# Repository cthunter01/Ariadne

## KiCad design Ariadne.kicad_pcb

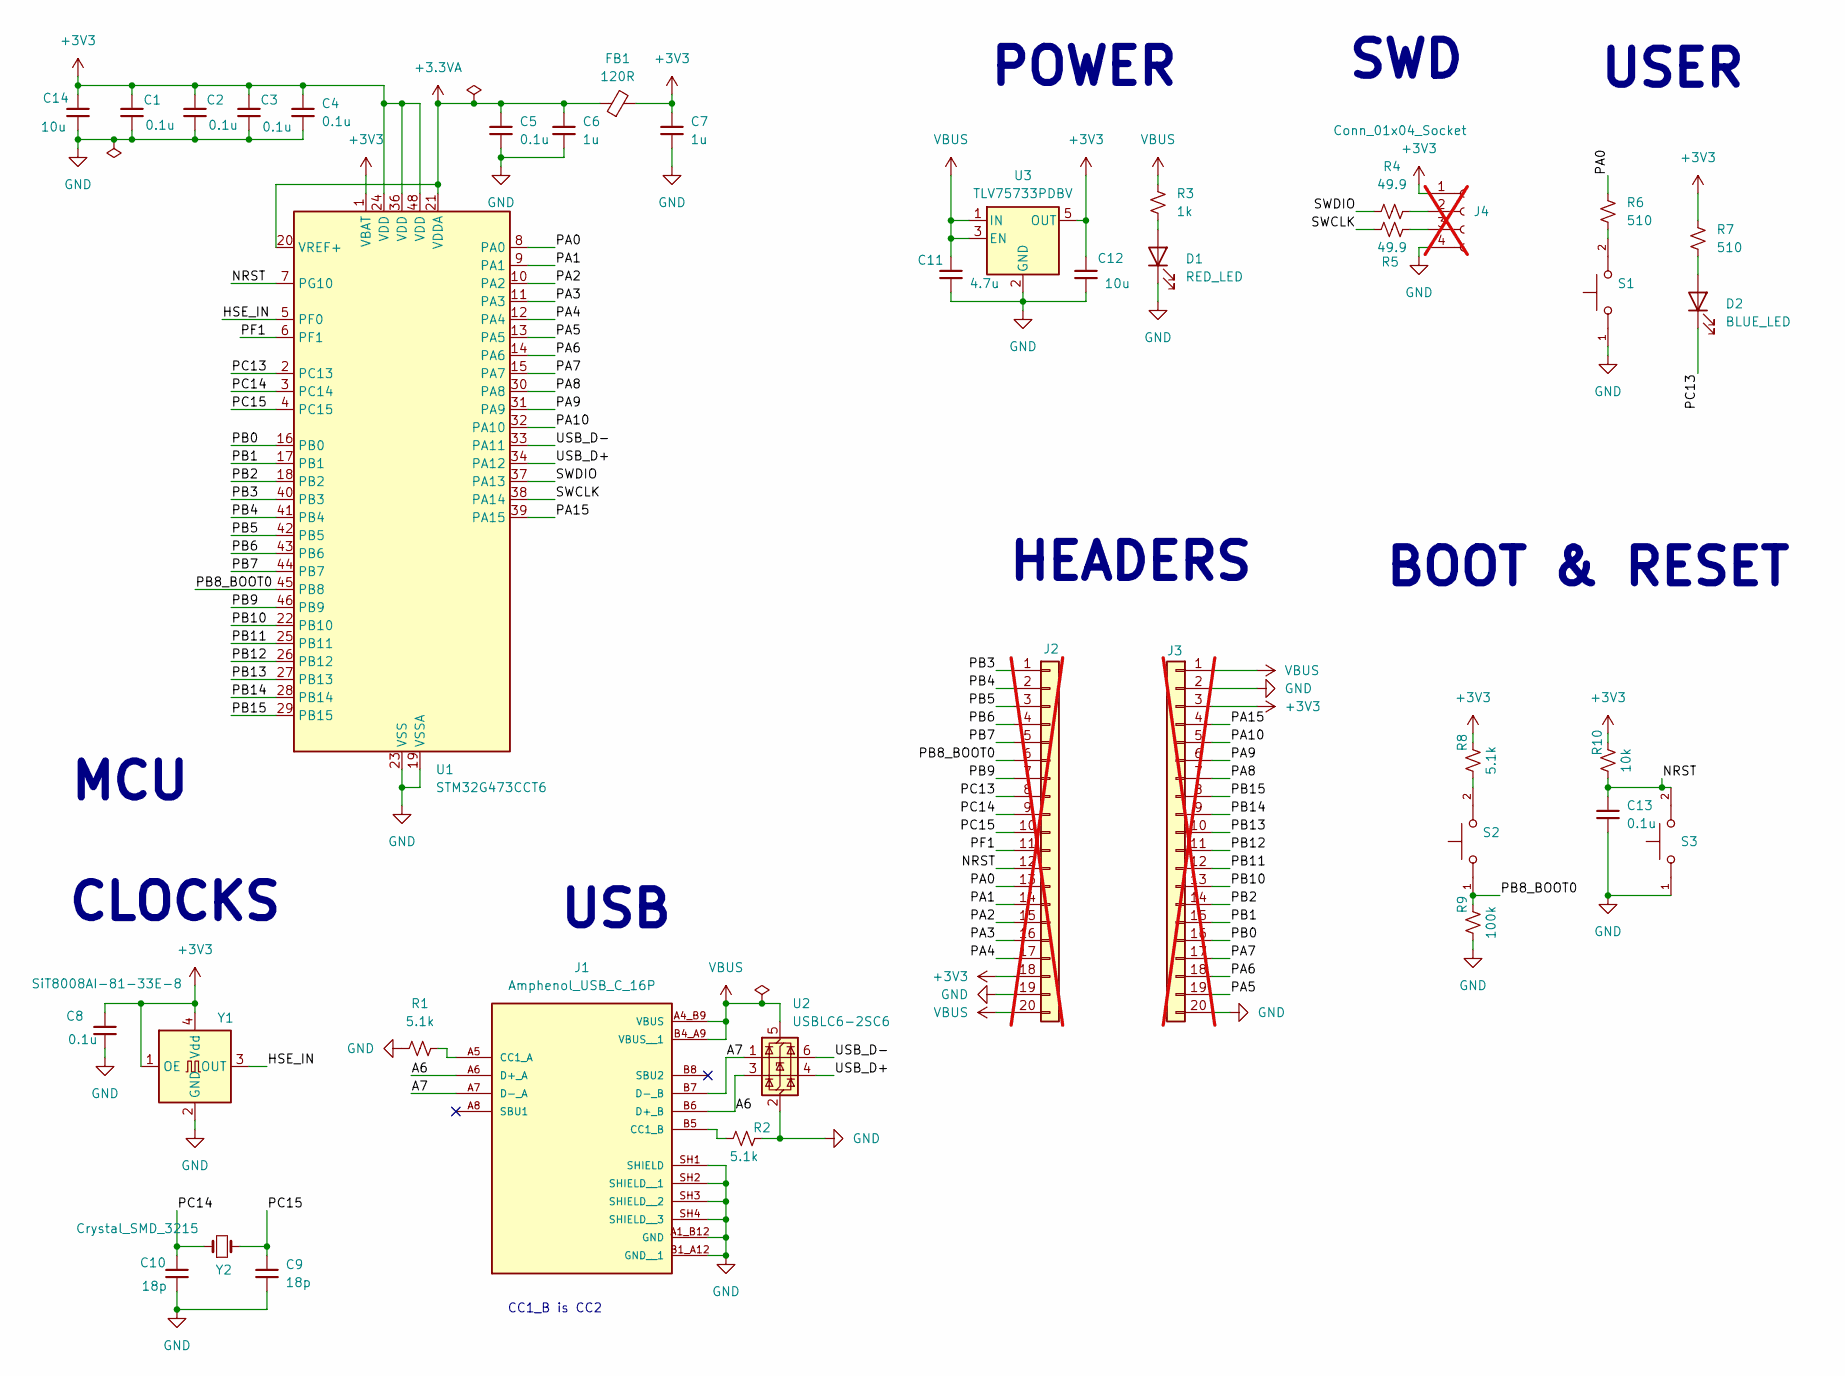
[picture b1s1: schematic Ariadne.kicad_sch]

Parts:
C1, C2, C3, C4, C5, C8, C13: 0.1u; C_0402_1005Metric; MPN CL05B104KO5NNNC; LCSC Part # C1525
C6, C7: 1u; C_0402_1005Metric; MPN CL05A105KA5NQNC; LCSC Part # C52923
C9, C10: 18p; C_0402_1005Metric; MPN 0402CG180J500NT; LCSC Part # C1549
C11: 4.7u; C_0402_1005Metric; MPN CL05A475MO5NUNC; LCSC Part # C318563
C12: 10u; C_0402_1005Metric; MPN CL05A106MP5NUNC; LCSC Part # C315248
C14: 10u; C_0603_1608Metric; MPN CL10A106KP8NNNC; LCSC Part # C19702
D1: RED_LED; LED_0402_1005Metric; MPN MHT136CRCT; LCSC Part # C397045
D2: BLUE_LED; LED_0402_1005Metric; MPN NCD0402B1; LCSC Part # C130724
FB1: 120R; IND_BLM18_0603_MUR; MPN BLM18PG121SN1D; LCSC Part # C14709
J1: Amphenol_USB_C_16P; AMPHENOL_12402012E212A; PARTREV 4; LCSC Part # C5150972
J2, J3: Conn_01x20; PinHeader_1x20_P2.54mm_Vertical; not fitted
J4: Conn_01x04_Socket; PinSocket_1x04_P2.54mm_Horizontal; not fitted
R1, R2, R8: 5.1k; R_0402_1005Metric; MPN 0402WGF5101TCE; LCSC Part # C25905
R3: 1k; R_0402_1005Metric; MPN 0402WGF1001TCE; LCSC Part # C11702
R4, R5: 49.9; R_0402_1005Metric; MPN 0402WGF499JTCE; LCSC Part # C25120
R6, R7: 510; R_0402_1005Metric; MPN 0402WGF5100TCE; LCSC Part # C25123
R9: 100k; R_0402_1005Metric; MPN 0402WGF1003TCE; LCSC Part # C25741
R10: 10k; R_0402_1005Metric; MPN 0402WGF1002TCE; LCSC Part # C25744
S1, S2, S3: TS-1088R-02026; SW_SWT0110-020010SSA_REVA; PARTREV A; LCSC Part # C455280
U1: STM32G473CCT6; STM32G473CCT3; MPN STM32G473CCT6; LCSC Part # C730112
U2: USBLC6-2SC6; SOT-23-6; MPN USBLC6-2SC6; LCSC Part # C7519
U3: TLV75733PDBV; SOT-23-5; MPN TLV75733PDBVR; LCSC Part # C485517
Y1: SiT8008AI-81-33E-8; Oscillator_SMD_SiT_PQFN-4Pin_7.0x5.0mm; MPN SiT8008AI-81-33E-8.000000; LCSC Part # C825363
Y2: Crystal_SMD_3215; Crystal_SMD_3215-2Pin_3.2x1.5mm; MPN Q13FC13500004; LCSC Part # C32346

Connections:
+3.3VA: C5.1, C6.1, FB1.1, U1.20 (VREF+), U1.21 (VDDA)
+3V3: C1.1, C2.1, C3.1, C4.1, C7.1, C8.1, C12.1, C14.1, FB1.2, J2.18, J3.3, J4.1, R7.1, R8.1, R10.1, U1.1 (VBAT), U1.24 (VDD), U1.36 (VDD), U1.48 (VDD), U3.5 (OUT), Y1.1 (OE), Y1.4 (Vdd)
/A6: J1.A6 (D+_A), J1.B6 (D+_B), U2.3 (I/O2)
/A7: J1.A7 (D-_A), J1.B7 (D-_B), U2.1 (I/O1)
/HSE_IN: U1.5 (PF0), Y1.3 (OUT)
/NRST: C13.1, J2.12, R10.2, S3.2, U1.7 (PG10)
/PA0: J2.13, R6.1, U1.8 (PA0)
/PA1: J2.14, U1.9 (PA1)
/PA2: J2.15, U1.10 (PA2)
/PA3: J2.16, U1.11 (PA3)
/PA4: J2.17, U1.12 (PA4)
/PA5: J3.19, U1.13 (PA5)
/PA6: J3.18, U1.14 (PA6)
/PA7: J3.17, U1.15 (PA7)
/PA8: J3.7, U1.30 (PA8)
/PA9: J3.6, U1.31 (PA9)
/PA10: J3.5, U1.32 (PA10)
/PA15: J3.4, U1.39 (PA15)
/PB0: J3.16, U1.16 (PB0)
/PB1: J3.15, U1.17 (PB1)
/PB2: J3.14, U1.18 (PB2)
/PB3: J2.1, U1.40 (PB3)
/PB4: J2.2, U1.41 (PB4)
/PB5: J2.3, U1.42 (PB5)
/PB6: J2.4, U1.43 (PB6)
/PB7: J2.5, U1.44 (PB7)
/PB8_BOOT0: J2.6, R9.1, S2.1, U1.45 (PB8)
/PB9: J2.7, U1.46 (PB9)
/PB10: J3.13, U1.22 (PB10)
/PB11: J3.12, U1.25 (PB11)
/PB12: J3.11, U1.26 (PB12)
/PB13: J3.10, U1.27 (PB13)
/PB14: J3.9, U1.28 (PB14)
/PB15: J3.8, U1.29 (PB15)
/PC13: D2.1 (K), J2.8, U1.2 (PC13)
/PC14: C10.1, J2.9, U1.3 (PC14), Y2.1
/PC15: C9.1, J2.10, U1.4 (PC15), Y2.2
/PF1: J2.11, U1.6 (PF1)
/SWCLK: R5.2, U1.38 (PA14)
/SWDIO: R4.1, U1.37 (PA13)
/USB_D+: U1.34 (PA12), U2.4 (I/O2)
/USB_D-: U1.33 (PA11), U2.6 (I/O1)
GND: C1.2, C2.2, C3.2, C4.2, C5.2, C6.2, C7.2, C8.2, C9.2, C10.2, C11.2, C12.2, C13.2, C14.2, D1.1 (K), J1.A1_B12 (GND), J1.B1_A12 (GND__1), J1.SH1 (SHIELD), J1.SH2 (SHIELD__1), J1.SH3 (SHIELD__2), J1.SH4 (SHIELD__3), J2.19, J3.2, J3.20, J4.4, R1.1, R2.1, R9.2, S1.1, S3.1, U1.19 (VSSA), U1.23 (VSS), U1.35 (VSS), U1.47 (VSS), U2.2 (GND), U3.2 (GND), Y1.2 (GND)
unnamed: D1.2 (A), R3.2
unnamed: D2.2 (A), R7.2
unnamed: J1.A5 (CC1_A), R1.2
unnamed: J1.B5 (CC1_B), R2.2
unnamed: J4.2, R4.2
unnamed: J4.3, R5.1
unnamed: R6.2, S1.2
unnamed: R8.2, S2.2
VBUS: C11.1, J1.A4_B9 (VBUS), J1.B4_A9 (VBUS__1), J2.20, J3.1, R3.1, U2.5 (VBUS), U3.1 (IN), U3.3 (EN)

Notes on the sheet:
POWER
CLOCKS
BOOT & RESET
HEADERS
USER
CC1_B is CC2
SWD
MCU
USB

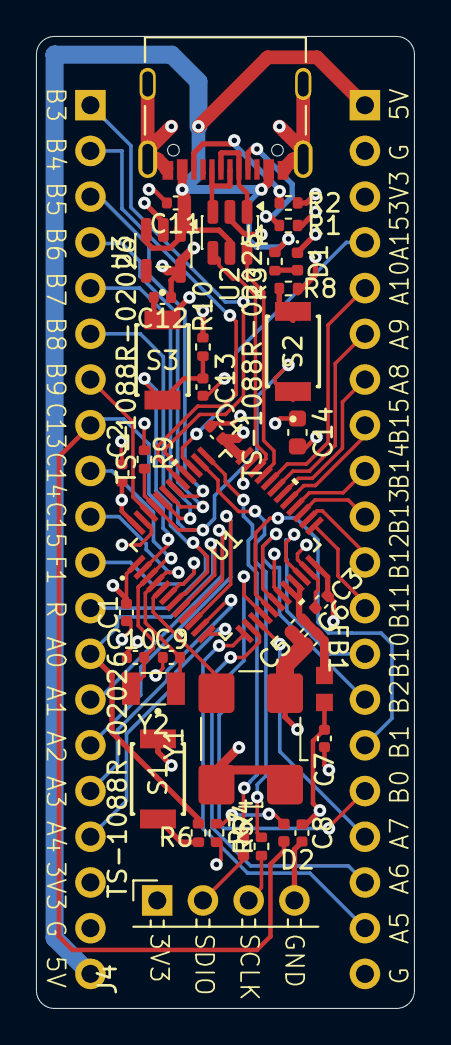
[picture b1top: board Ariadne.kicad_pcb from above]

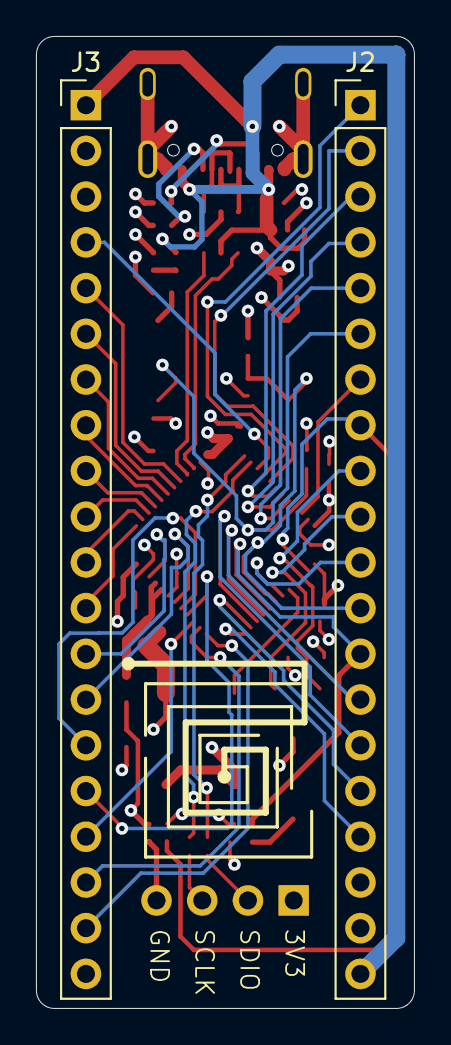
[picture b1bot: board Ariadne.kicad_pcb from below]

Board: 4 copper layers, 21.0 x 54.0 mm, 39 parts (2 on the bottom side), 52 nets.

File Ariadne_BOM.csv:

"Designator","Qty","Comment","MANUFACTURER","MPN","LCSC Part #","DNP","Exclude from BOM","Exclude from Board","Exclude from Simulation","Footprint","Datasheet"
"C1,C2,C3,C4,C5,C8,C13","7","0.1u","Samsung Electro-Mechanics","CL05B104KO5NNNC","C1525","","","","","Ariadne:C_0402_1005Metric",""
"C6,C7","2","1u","Samsung Electro-Mechanics","CL05A105KA5NQNC","C52923","","","","","Ariadne:C_0402_1005Metric",""
"C9,C10","2","18p","FH (Guangdong Fenghua Advanced Tech)","0402CG180J500NT","C1549","","","","","Ariadne:C_0402_1005Metric",""
"C11","1","4.7u","Samsung Electro-Mechanics","CL05A475MO5NUNC","C318563","","","","","Ariadne:C_0402_1005Metric",""
"C12","1","10u","Samsung Electro-Mechanics","CL05A106MP5NUNC","C315248","","","","","Ariadne:C_0402_1005Metric",""
"C14","1","10u","Samsung Electro-Mechanics","CL10A106KP8NNNC","C19702","","","","","Ariadne:C_0603_1608Metric",""
"D1","1","RED_LED","MEIHUA","MHT136CRCT","C397045","","","","","Ariadne:LED_0402_1005Metric",""
"D2","1","BLUE_LED","Foshan NationStar Optoelectronics","NCD0402B1","C130724","","","","","Ariadne:LED_0402_1005Metric",""
"FB1","1","120R","Murata Electronics","BLM18PG121SN1D","C14709","","","","","Ariadne:IND_BLM18_0603_MUR",""
"J1","1","Amphenol_USB_C_16P","Amphenol","12402012E212A","C5150972","","","","","Ariadne:AMPHENOL_12402012E212A",""
"R1,R2,R8","3","5.1k","UNI-ROYAL(Uniroyal Elec)","0402WGF5101TCE","C25905","","","","","Ariadne:R_0402_1005Metric",""
"R3","1","1k","UNI-ROYAL(Uniroyal Elec)","0402WGF1001TCE","C11702","","","","","Ariadne:R_0402_1005Metric",""
"R4,R5","2","49.9","UNI-ROYAL(Uniroyal Elec)","0402WGF499JTCE","C25120","","","","","Ariadne:R_0402_1005Metric",""
"R6,R7","2","510","UNI-ROYAL(Uniroyal Elec)","0402WGF5100TCE","C25123","","","","","Ariadne:R_0402_1005Metric",""
"R9","1","100k","UNI-ROYAL(Uniroyal Elec)","0402WGF1003TCE","C25741","","","","","Ariadne:R_0402_1005Metric",""
"R10","1","10k","UNI-ROYAL(Uniroyal Elec)","0402WGF1002TCE","C25744","","","","","Ariadne:R_0402_1005Metric",""
"S1,S2,S3","3","TS-1088R-02026","XUNPU","TS-1088R-02026","C455280","","","","","Ariadne:SW_SWT0110-020010SSA_REVA",""
"U1","1","STM32G473CCT6","STMicroelectronics","STM32G473CCT6","C730112","","","","","Ariadne:STM32G473CCT3","${KIPRJMOD}/libraries/datasheets/stm32g473.pdf"
"U2","1","USBLC6-2SC6","STMicroelectronics","USBLC6-2SC6","C7519","","","","","Ariadne:SOT-23-6","https://www.st.com/resource/en/datasheet/usblc6-2.pdf"
"U3","1","TLV75733PDBV","Texas Instruments","TLV75733PDBVR","C485517","","","","","Ariadne:SOT-23-5","https://www.ti.com/lit/ds/symlink/tlv757p.pdf"
"Y1","1","SiT8008AI-81-33E-8","SiTime","SiT8008AI-81-33E-8.000000","C825363","","","","","Ariadne:Oscillator_SMD_SiT_PQFN-4Pin_7.0x5.0mm","${KIPRJMOD}/libraries/datasheets/SiT8008A.pdf"
"Y2","1","Crystal_SMD_3215","Epson Seiko","Q13FC13500004","C32346","","","","","Ariadne:Crystal_SMD_3215-2Pin_3.2x1.5mm",""
